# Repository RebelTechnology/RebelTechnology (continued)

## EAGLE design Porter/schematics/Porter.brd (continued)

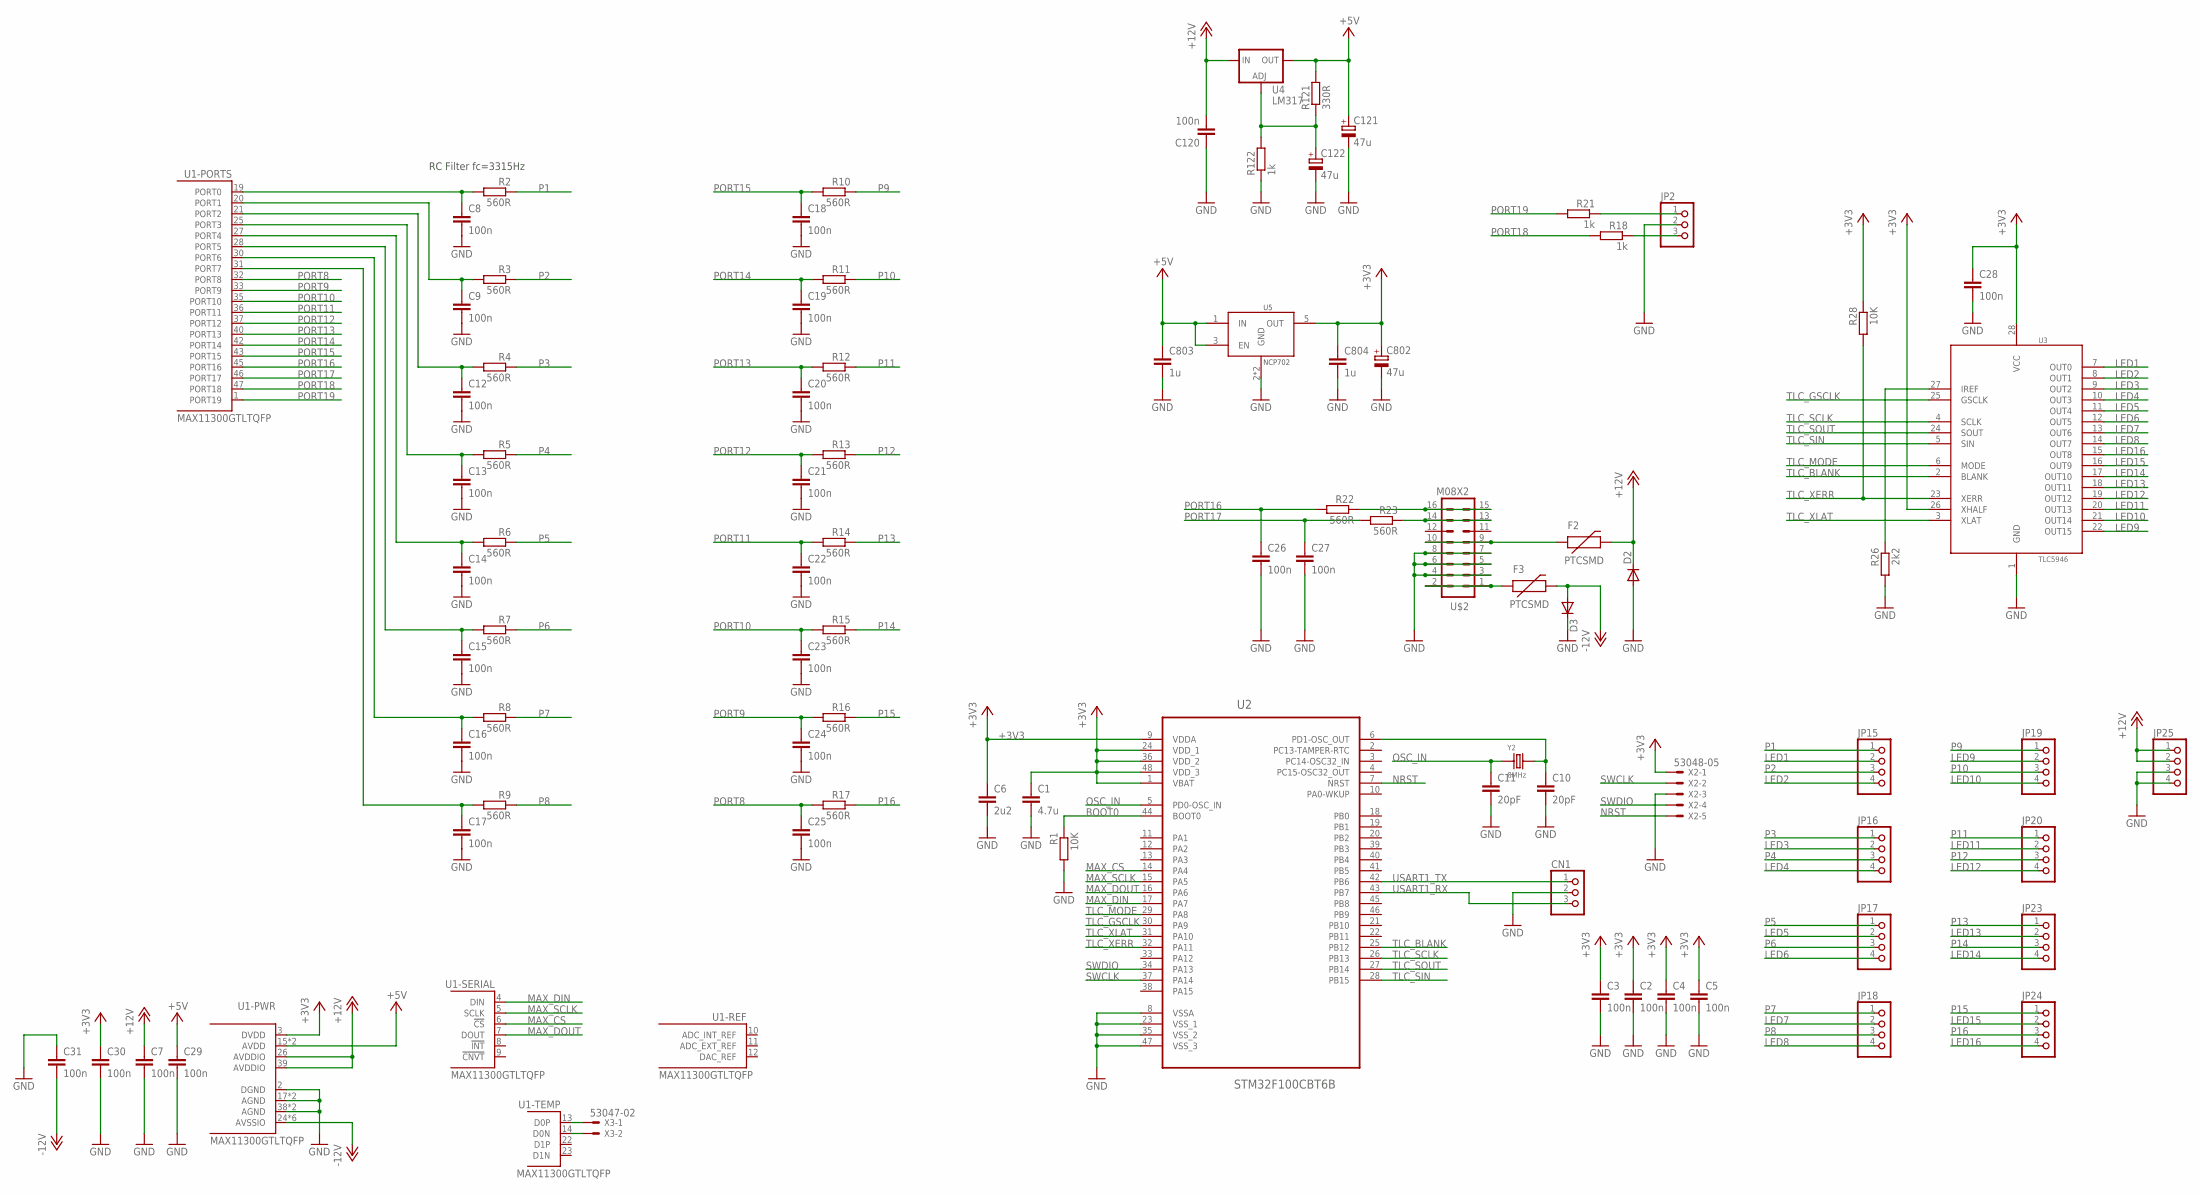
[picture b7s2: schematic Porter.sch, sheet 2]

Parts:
C1: 4.7u; C0603
C2, C3, C4, C5, C7, C8, C9, C12, C13, C14, C15, C16, C17, C18, C19, C20, C21, C22, C23, C24, C25, C26, C27, C28, C29, C30, C31, C120: 100n; C0603
C6: 2u2; C0603
C10, C11: 20pF; C0603
C121, C122, C802: 47u; CPOL-5
C803, C804: 1u; C0603
CN1: CON-JST-1X03PH-TH; JST-B3B-PH-KL
D2, D3: DIODESMA; SMA-DIODE
F2, F3: PTCSMD; PTC-1206
JP2: PINHD-1X3; 1X03
JP15, JP16, JP17, JP18, JP19, JP20, JP23, JP24, JP25: PINHD-1X4; 1X04
R1, R28: 10K; 0603
R2, R3, R4, R5, R6, R7, R8, R9, R10, R11, R12, R13, R14, R15, R16, R17, R22, R23: 560R; 0603
R18, R21, R122: 1k; 0603
R26: 2k2; 0603
R121: 330R; 0603
U1: MAX11300GTLTQFP; TQFP48
U2: STM32F100CBT6B; QFP50P900X900X160-48N
U3: TLC5946; TSSOP28
U4: LM317; SOT223
U5: NCP702; TSOP-5
U$2: M08X2; 2X8
X2: 53048-05
X3: 53047-02
Y2: 8MHz; X2-SMD-5.0X3.2X1.3MM

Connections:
+3V3: C1.1, C2.1, C3.1, C4.1, C5.1, C6.1, C28.1, C30.1, C802.+, C804.1, R28.1, U1.3 (DVDD), U2.1 (VBAT), U2.9 (VDDA), U2.24 (VDD_1), U2.36 (VDD_2), U2.48 (VDD_3), U3.26 (XHALF), U3.28 (VCC), U5.5 (OUT), X2.1
+5V: C29.1, C121.+, C803.1, R121.2, U1.15 (AVDD), U1.16 (AVDD), U4.2 (OUT), U4.4 (OUT), U5.1 (IN), U5.3 (EN)
+12V: C7.1, C120.2, D2.C, F2.2, JP25.1, JP25.2, U1.26 (AVDDIO), U1.39 (AVDDIO), U4.3 (IN)
-12V: C31.2, D3.A, F3.2, U1.24 (AVSSIO), U1.29 (AVSSIO), U1.34 (AVSSIO), U1.41 (AVSSIO), U1.44 (AVSSIO), U1.48 (AVSSIO)
BOOT0: R1.1, U2.44 (BOOT0)
GND: C1.2, C2.2, C3.2, C4.2, C5.2, C6.2, C7.2, C8.2, C9.2, C10.2, C11.2, C12.2, C13.2, C14.2, C15.2, C16.2, C17.2, C18.2, C19.2, C20.2, C21.2, C22.2, C23.2, C24.2, C25.2, C26.2, C27.2, C28.2, C29.2, C30.2, C31.1, C120.1, C121.-, C122.-, C802.-, C803.2, C804.2, CN1.2, D2.A, D3.C, JP2.2, JP25.3, JP25.4, R1.2, R26.2, R122.1, U1.2 (DGND), U1.17 (AGND), U1.18 (AGND), U1.38 (AGND), U1.EP (AGND), U2.8 (VSSA), U2.23 (VSS_1), U2.35 (VSS_2), U2.47 (VSS_3), U3.1 (GND), U5.2 (GND), U5.4 (GND), U$2.3, U$2.4, U$2.5, U$2.6, U$2.7, U$2.8, X2.3
LED1: JP15.2, U3.7 (OUT0)
LED2: JP15.4, U3.8 (OUT1)
LED3: JP16.2, U3.9 (OUT2)
LED4: JP16.4, U3.10 (OUT3)
LED5: JP17.2, U3.11 (OUT4)
LED6: JP17.4, U3.12 (OUT5)
LED7: JP18.2, U3.13 (OUT6)
LED8: JP18.4, U3.14 (OUT7)
LED9: JP19.2, U3.22 (OUT15)
LED10: JP19.4, U3.21 (OUT14)
LED11: JP20.2, U3.20 (OUT13)
LED12: JP20.4, U3.19 (OUT12)
LED13: JP23.2, U3.18 (OUT11)
LED14: JP23.4, U3.17 (OUT10)
LED15: JP24.2, U3.16 (OUT9)
LED16: JP24.4, U3.15 (OUT8)
MAX_CS: U1.6 (!CS!), U2.14 (PA4)
MAX_DIN: U1.4 (DIN), U2.17 (PA7)
MAX_DOUT: U1.7 (DOUT), U2.16 (PA6)
MAX_SCLK: U1.5 (SCLK), U2.15 (PA5)
unnamed: C10.1, U2.6 (PD1-OSC_OUT), Y2.2
unnamed: JP2.1, R21.1
unnamed: F3.1, U$2.1, U$2.2
unnamed: JP2.3, R18.1
unnamed: R22.1, U$2.15, U$2.16
unnamed: U1.13 (D0P), X3.1
unnamed: U1.14 (D0N), X3.2
unnamed: C122.+, R121.1, R122.2, U4.1 (ADJ)
unnamed: R23.1, U$2.13, U$2.14
unnamed: R26.1, U3.27 (IREF)
unnamed: F2.1, U$2.9, U$2.10
NRST: U2.7 (NRST), X2.5
OSC_IN: C11.1, U2.5 (PD0-OSC_IN), Y2.1
P1: JP15.1, R2.1
P2: JP15.3, R3.1
P3: JP16.1, R4.1
P4: JP16.3, R5.1
P5: JP17.1, R6.1
P6: JP17.3, R7.1
P7: JP18.1, R8.1
P8: JP18.3, R9.1
P9: JP19.1, R10.1
P10: JP19.3, R11.1
P11: JP20.1, R12.1
P12: JP20.3, R13.1
P13: JP23.1, R14.1
P14: JP23.3, R15.1
P15: JP24.1, R16.1
P16: JP24.3, R17.1
PORT0: C8.1, R2.2, U1.19 (PORT0)
PORT1: C9.1, R3.2, U1.20 (PORT1)
PORT2: C12.1, R4.2, U1.21 (PORT2)
PORT3: C13.1, R5.2, U1.25 (PORT3)
PORT4: C14.1, R6.2, U1.27 (PORT4)
PORT5: C15.1, R7.2, U1.28 (PORT5)
PORT6: C16.1, R8.2, U1.30 (PORT6)
PORT7: C17.1, R9.2, U1.31 (PORT7)
PORT8: C25.1, R17.2, U1.32 (PORT8)
PORT9: C24.1, R16.2, U1.33 (PORT9)
PORT10: C23.1, R15.2, U1.35 (PORT10)
PORT11: C22.1, R14.2, U1.36 (PORT11)
PORT12: C21.1, R13.2, U1.37 (PORT12)
PORT13: C20.1, R12.2, U1.40 (PORT13)
PORT14: C19.1, R11.2, U1.42 (PORT14)
PORT15: C18.1, R10.2, U1.43 (PORT15)
PORT16: C26.1, R22.2, U1.45 (PORT16)
PORT17: C27.1, R23.2, U1.46 (PORT17)
PORT18: R18.2, U1.47 (PORT18)
PORT19: R21.2, U1.1 (PORT19)
SWCLK: U2.37 (PA14), X2.2
SWDIO: U2.34 (PA13), X2.4
TLC_BLANK: U2.25 (PB12), U3.2 (BLANK)
TLC_GSCLK: U2.30 (PA9), U3.25 (GSCLK)
TLC_MODE: U2.29 (PA8), U3.6 (MODE)
TLC_SCLK: U2.26 (PB13), U3.4 (SCLK)
TLC_SIN: U2.28 (PB15), U3.5 (SIN)
TLC_SOUT: U2.27 (PB14), U3.24 (SOUT)
TLC_XERR: R28.2, U2.32 (PA11), U3.23 (XERR)
TLC_XLAT: U2.31 (PA10), U3.3 (XLAT)
USART1_RX: CN1.3, U2.43 (PB7)
USART1_TX: CN1.1, U2.42 (PB6)

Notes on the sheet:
RC Filter fc=3315Hz

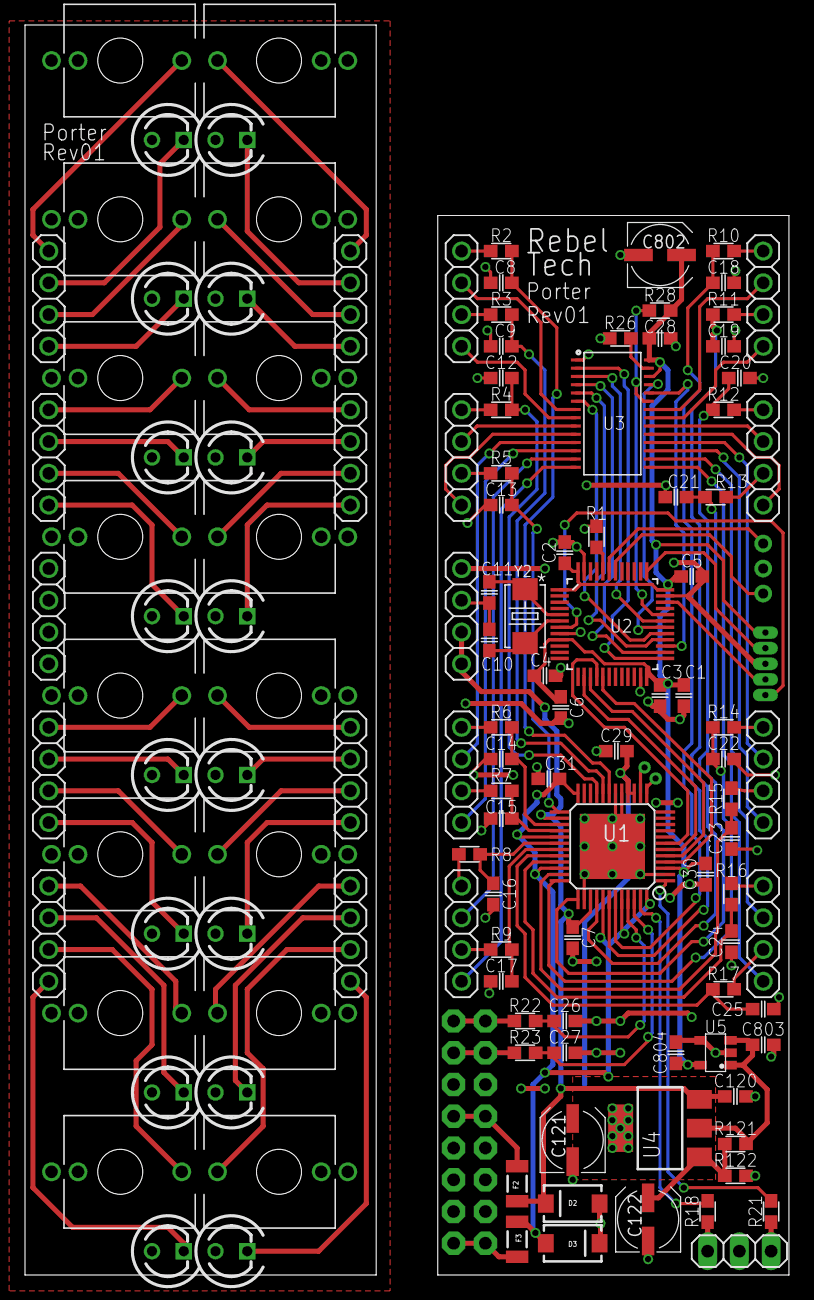
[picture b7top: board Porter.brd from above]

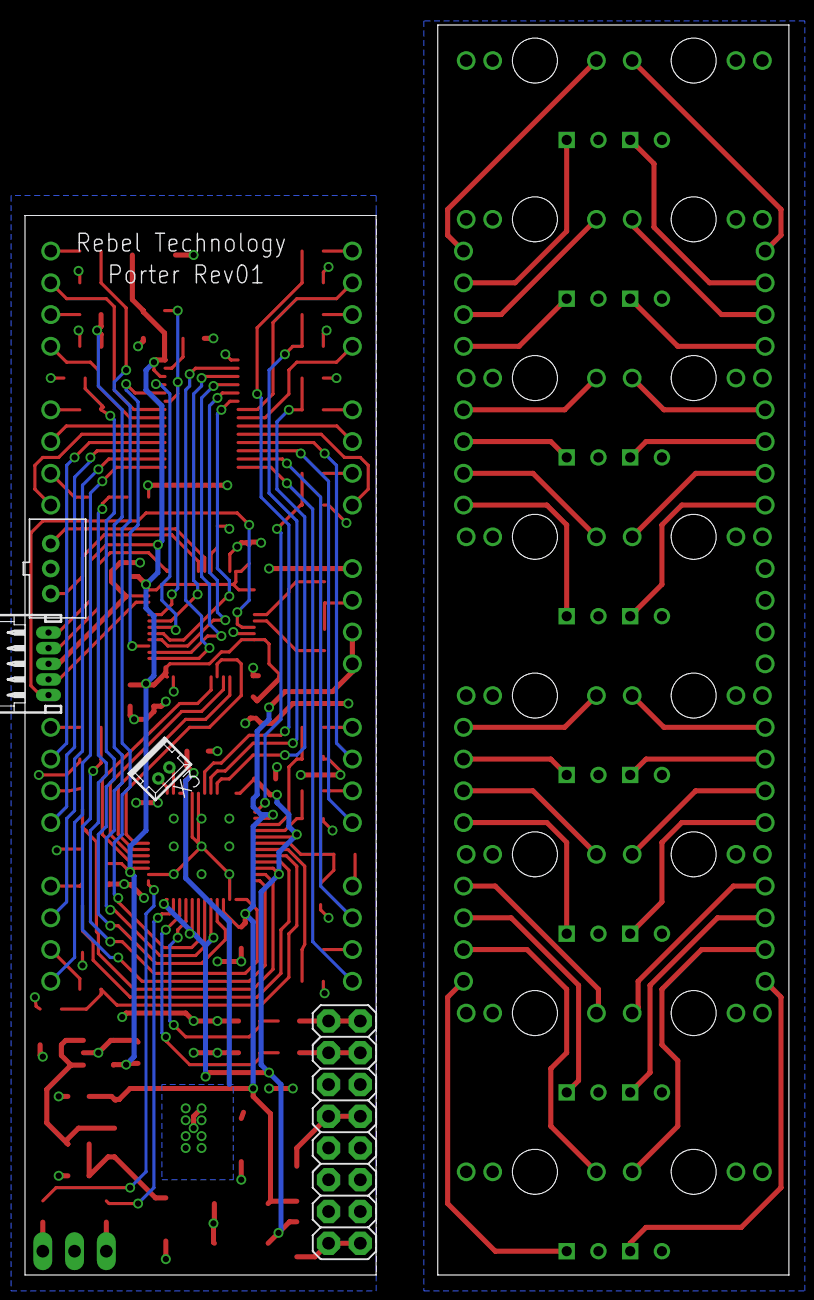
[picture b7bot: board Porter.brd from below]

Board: 2 copper layers, 61.1 x 100.0 mm, 127 parts (4 on the bottom side), 121 nets.

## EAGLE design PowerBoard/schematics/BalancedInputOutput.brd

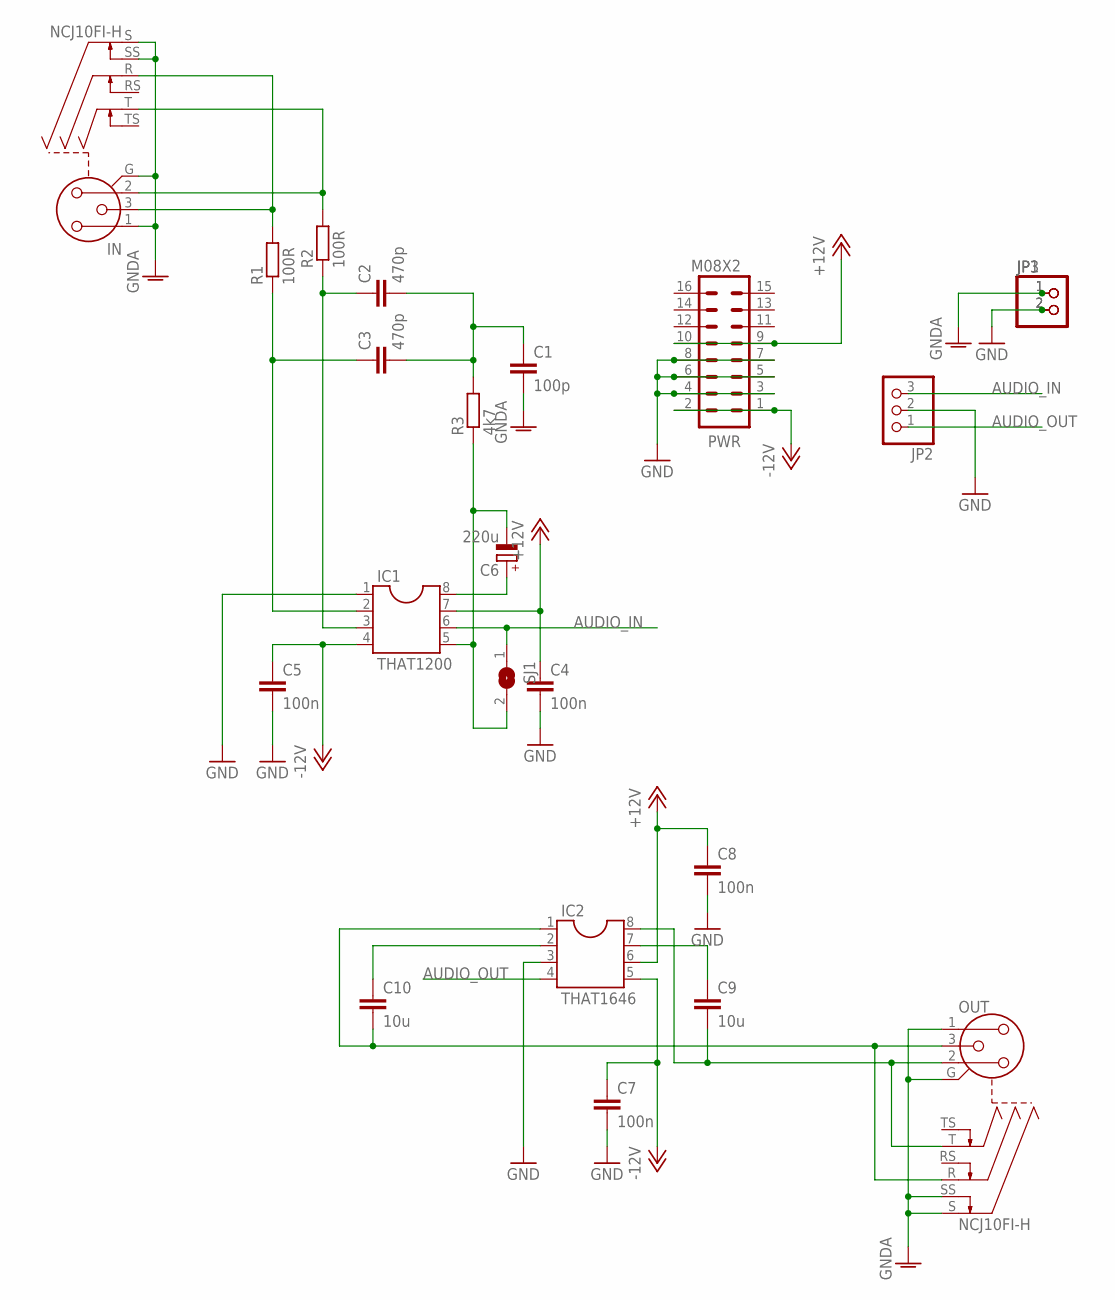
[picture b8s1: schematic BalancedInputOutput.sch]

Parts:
C1: 100p; C050-025X075
C2, C3: 470p; C050-025X075
C4, C5, C7, C8: 100n; C050-025X075
C6: 220u; E5-8,5
C9, C10: 10u; C050-025X075
IC1: THAT1200; DIL08
IC2: THAT1646; DIL08
IN: NCJ10FI-H
JP1, JP3: PINHD-1X2; 1X02
JP2: PINHD-1X3; 1X03
OUT: NCJ10FI-H
PWR: M08X2; 2X8
R1, R2: 100R; 0207/7
R3: 4k7; 0207/7
SJ1: SJW

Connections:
+12V: C4.1, C8.1, IC1.7, IC2.6, PWR.9, PWR.10
-12V: C5.1, C7.1, IC1.4, IC2.5, PWR.1, PWR.2
AUDIO_IN: IC1.6, JP2.3, SJ1.1
AUDIO_OUT: IC2.4, JP2.1
GND: C4.2, C5.2, C7.2, C8.2, IC1.1, IC2.3, JP1.2, JP2.2, JP3.2, PWR.3, PWR.4, PWR.5, PWR.6, PWR.7, PWR.8
GNDA: C1.2, IN.1, IN.G, IN.S, IN.SS, JP1.1, JP3.1, OUT.1, OUT.G, OUT.S, OUT.SS
unnamed: C3.1, IC1.2, R1.1
unnamed: IN.3, IN.R, R1.2
unnamed: C2.1, IC1.3, R2.1
unnamed: IN.2, IN.T, R2.2
unnamed: C6.-, IC1.5, R3.1, SJ1.2
unnamed: C1.1, C2.2, C3.2, R3.2
unnamed: C9.1, IC2.7
unnamed: C10.1, IC2.2
unnamed: C6.+, IC1.8
unnamed: C9.2, IC2.8, OUT.2, OUT.T
unnamed: C10.2, IC2.1, OUT.3, OUT.R

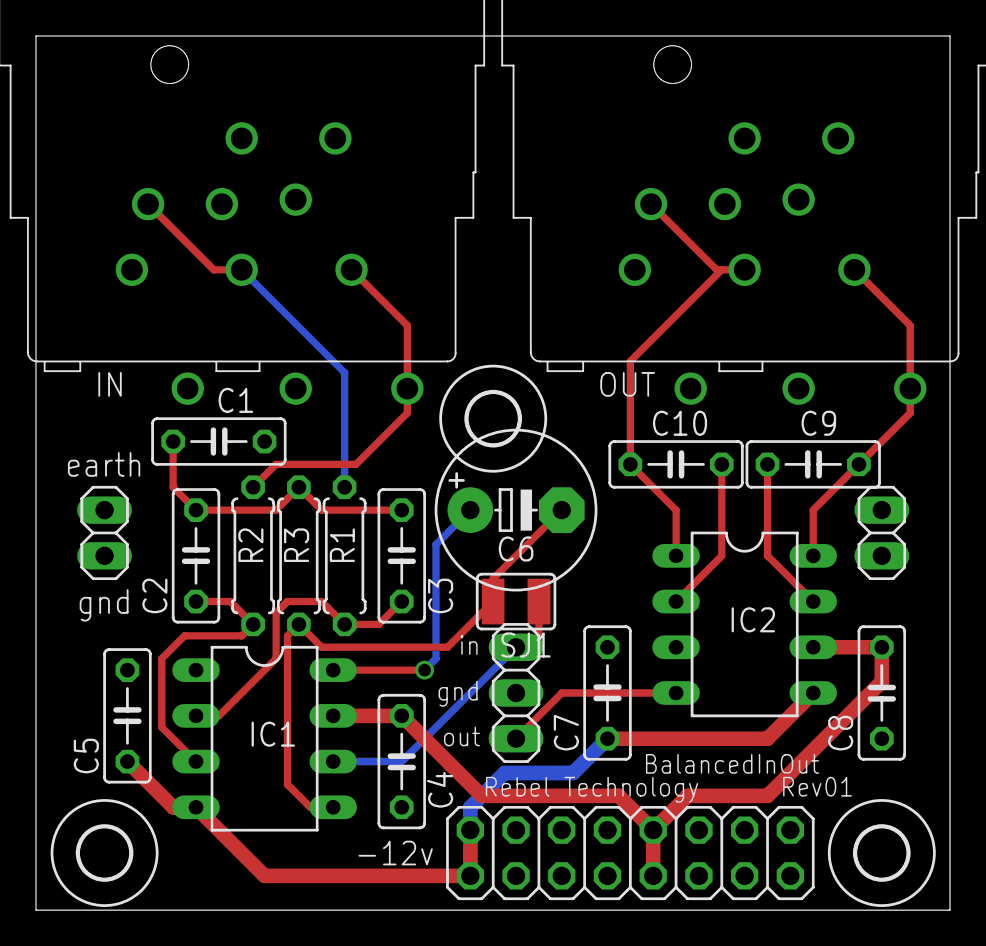
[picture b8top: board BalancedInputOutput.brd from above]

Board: 2 copper layers, 50.8 x 48.6 mm, 25 parts (0 on the bottom side), 17 nets.

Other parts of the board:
U$1, U$2, U$3: 2,8

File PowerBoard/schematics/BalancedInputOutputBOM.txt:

Partlist exported from D:/Drive/Work/Rebel/ProjectFiles/RebelTechnology/PowerBoard/schematics/BalancedInputOutput.sch at 13/04/2015 14:58:14

Qty Value     Device          Package      Parts          Description                          
2             PINHD-1X2       1X02         JP1, JP3       PIN HEADER                           
1             PINHD-1X3       1X03         JP2            PIN HEADER                           
1             SJW             SJW          SJ1            SMD solder JUMPER                    
2   100R      R-EU_0207/7     0207/7       R1, R2         RESISTOR, European symbol            
4   100n      C-EU050-025X075 C050-025X075 C4, C5, C7, C8 CAPACITOR, European symbol           
1   100p      C-EU050-025X075 C050-025X075 C1             CAPACITOR, European symbol           
2   10u       C-EU050-025X075 C050-025X075 C9, C10        CAPACITOR, European symbol           
1   220u      CPOL-EUE5-8.5   E5-8,5       C6             POLARIZED CAPACITOR, European symbol 
2   470p      C-EU050-025X075 C050-025X075 C2, C3         CAPACITOR, European symbol           
1   4k7       R-EU_0207/7     0207/7       R3             RESISTOR, European symbol            
1   M08X2     M08X2           2X8          PWR                                                 
2   NCJ10FI-H NCJ10FI-H       NCJ10FI-H    IN, OUT        Neutrik Audio Connector XLR SERIES   
1   THAT1200  DIL8            DIL08        IC1            Dual In Line / Socket                
1   THAT1646  DIL8            DIL08        IC2            Dual In Line / Socket
